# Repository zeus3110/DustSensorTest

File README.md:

# DustSensorTest
Dust sensor (SHARP GP2Y1010AU0F) test circuit
1st Release

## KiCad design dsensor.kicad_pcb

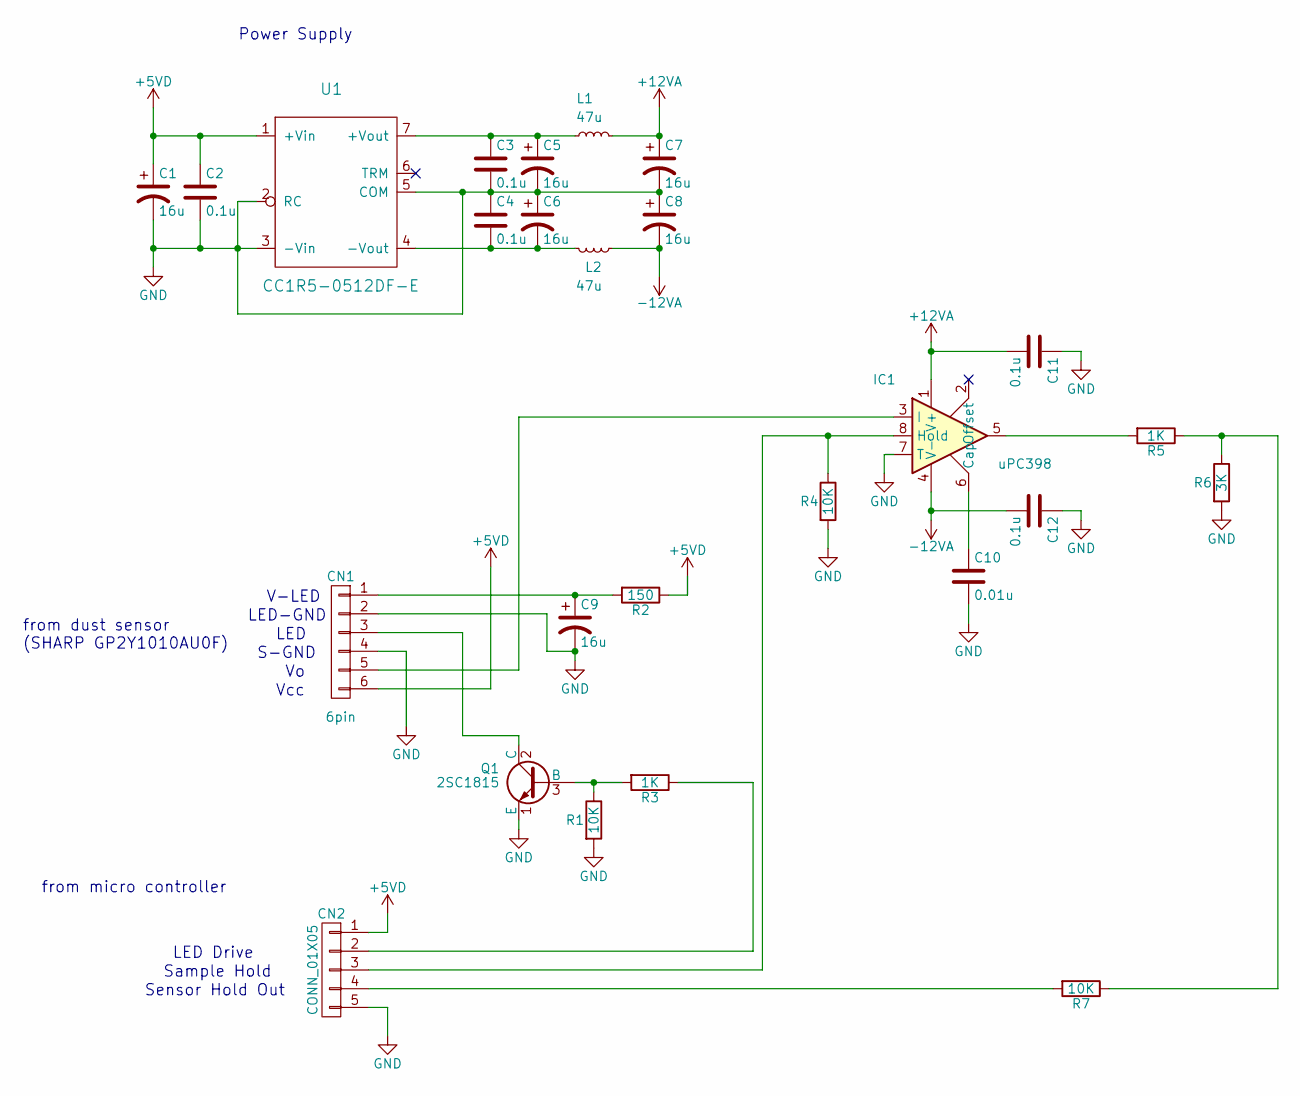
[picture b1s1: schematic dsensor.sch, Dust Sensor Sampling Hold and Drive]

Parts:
C1, C5, C6, C7, C8, C9: 16u; C_Radial_D5_L6_P2.5
C2, C3, C4, C11, C12: 0.1u; C_0603
C10: 0.01u; C_Rect_L4_W2.5_P2.5
CN1: 6pin; Pin_Header_Straight_1x06
CN2: CONN_01X05; Pin_Header_Straight_1x05
IC1: uPC398; PDIP-8
L1, L2: 47u; INDUCTOR_V
Q1: 2SC1815; TO-92_Molded_Narrow
R1, R4, R7: 10K; R_0603
R2: 150; R_0603
R3, R5: 1K; R_0603
R6: 3K; R_0603
U1: CC1R5-0512DF-E; CC1R5

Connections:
+5VD: C1.1, C2.1, CN1.6, CN2.1, R2.1, U1.1 (+Vin)
+12VA: C7.1, C11.2, IC1.1 (V+), L1.2
-12VA: C8.2, C12.2, IC1.4 (V-), L2.1
GND: C1.2, C2.2, C3.2, C4.1, C5.2, C6.1, C7.2, C8.1, C9.2, C10.2, C11.1, C12.1, CN1.2, CN1.4, CN2.5, IC1.7 (T), Q1.1 (E), R1.2, R4.2, R6.2, U1.2 (RC), U1.3 (-Vin), U1.5 (COM)
unnamed: C3.1, C5.1, L1.1, U1.7 (+Vout)
unnamed: C4.2, C6.2, L2.2, U1.4 (-Vout)
unnamed: C9.1, CN1.1, R2.2
unnamed: C10.1, IC1.6 (Cap)
unnamed: CN1.3, Q1.2 (C)
unnamed: CN1.5, IC1.3 (I)
unnamed: CN2.2, R3.1
unnamed: CN2.3, IC1.8 (Hold), R4.1
unnamed: CN2.4, R7.2
unnamed: IC1.5, R5.2
unnamed: Q1.3 (B), R1.1, R3.2
unnamed: R5.1, R6.1, R7.1

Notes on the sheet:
Power Supply
V-LED
LED-GND
LED
S-GND
Vcc
from dust sensor (SHARP GP2Y1010AU0F)
from micro controller
LED Drive
Sample Hold
Sensor Hold Out

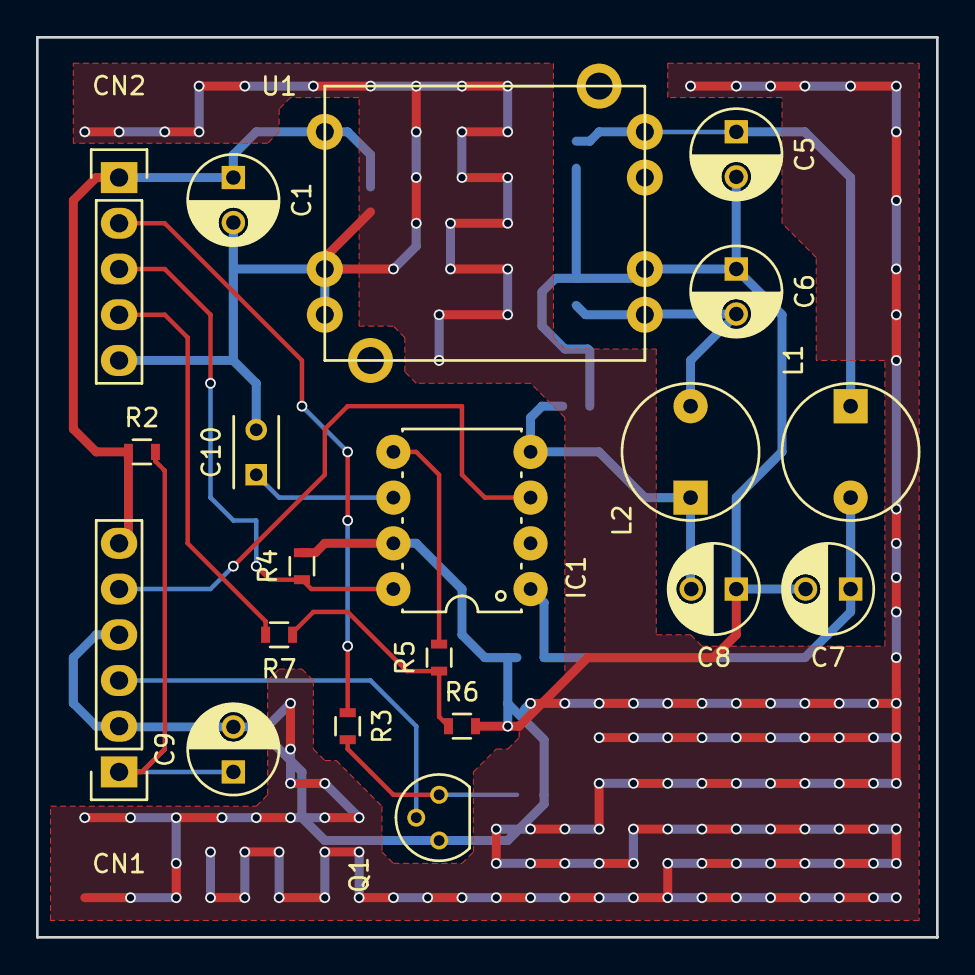
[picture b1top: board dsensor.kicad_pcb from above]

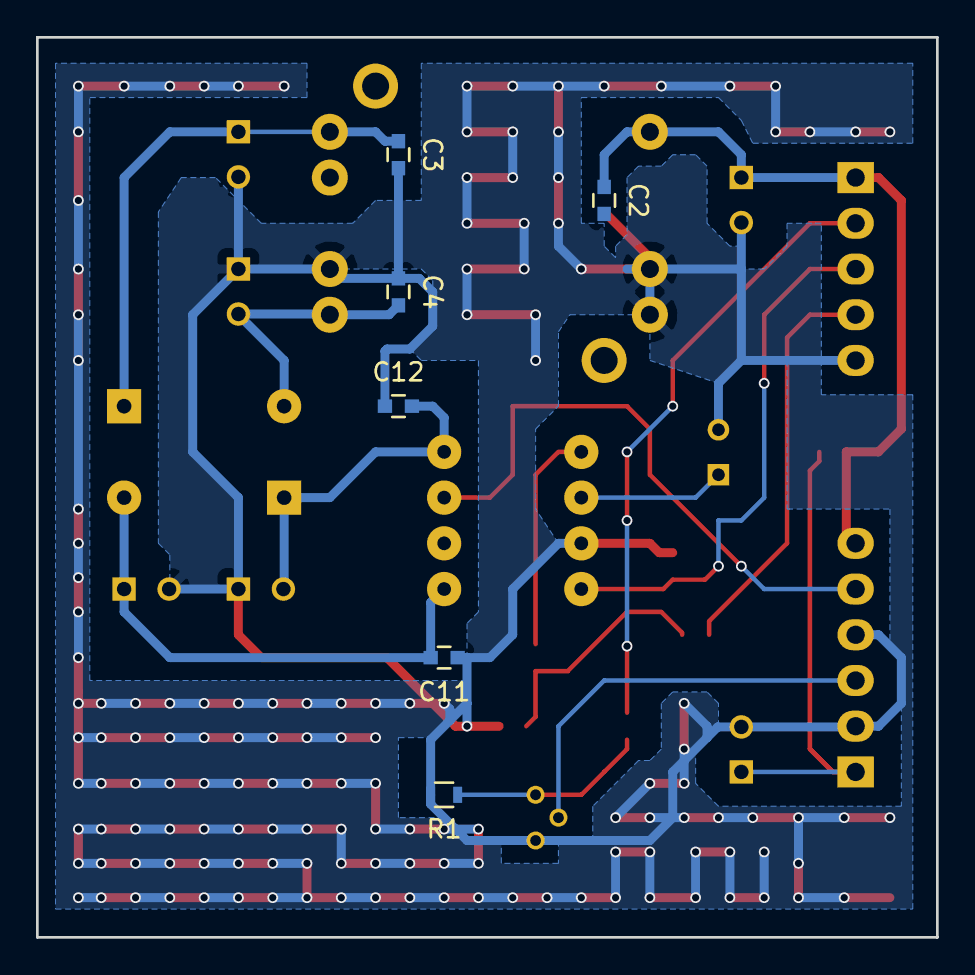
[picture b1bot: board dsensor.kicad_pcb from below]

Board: 2 copper layers, 50.0 x 50.0 mm, 26 parts (6 on the bottom side), 16 nets.

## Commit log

2016-11-28 :circus_tent: Added .gitattributes & .gitignore files
2016-11-28 1st Release
    1st Release
2016-11-28 PDF added
2016-12-11 Changed
    c & r value changed
